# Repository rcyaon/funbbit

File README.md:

# Funbbit

A modern recreation of the Sony PET-F7 "Funbbit" (1998): a virtual-pet
accessory for a Walkman (or any 3.5 mm player). It sits inline between the
player and the headphones, taps the audio without disturbing it, and animates
a pet on a 1.28" Sharp monochrome memory LCD. The pet dances while music plays
("dancing pet", "weight battle") and gets fat when it does not. An STM32U083
runs everything from a single **CR2032** coin cell.

## Renders

| Top | Bottom |
| --- | --- |
|  |  |

44 x 72 mm, 2 layers, black mask, white silkscreen. The Sharp LCD (fitted by
hand into J4) and the CR2032 cell are not shown. 

## Pixel art

Pet sprites are drawn in [Aseprite](https://www.aseprite.org/).

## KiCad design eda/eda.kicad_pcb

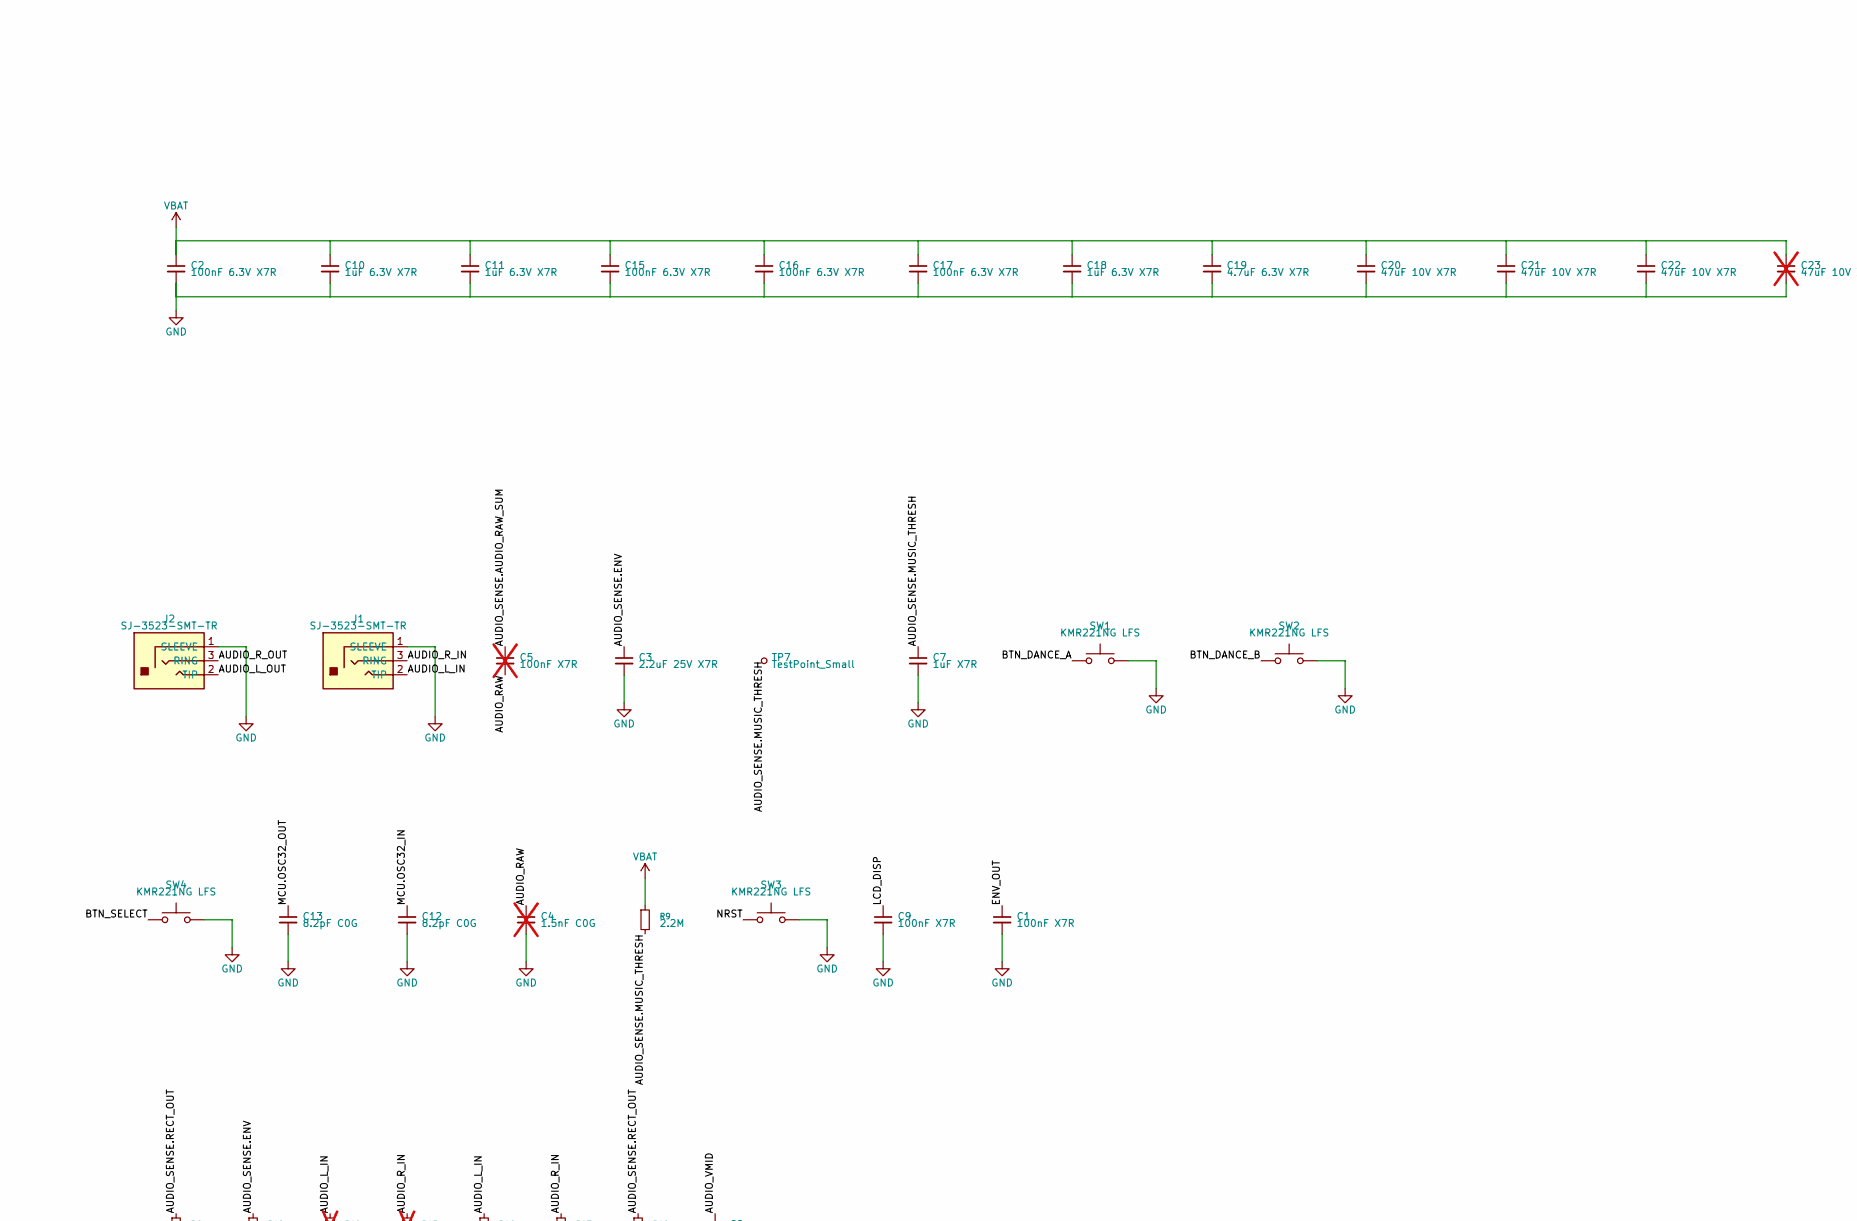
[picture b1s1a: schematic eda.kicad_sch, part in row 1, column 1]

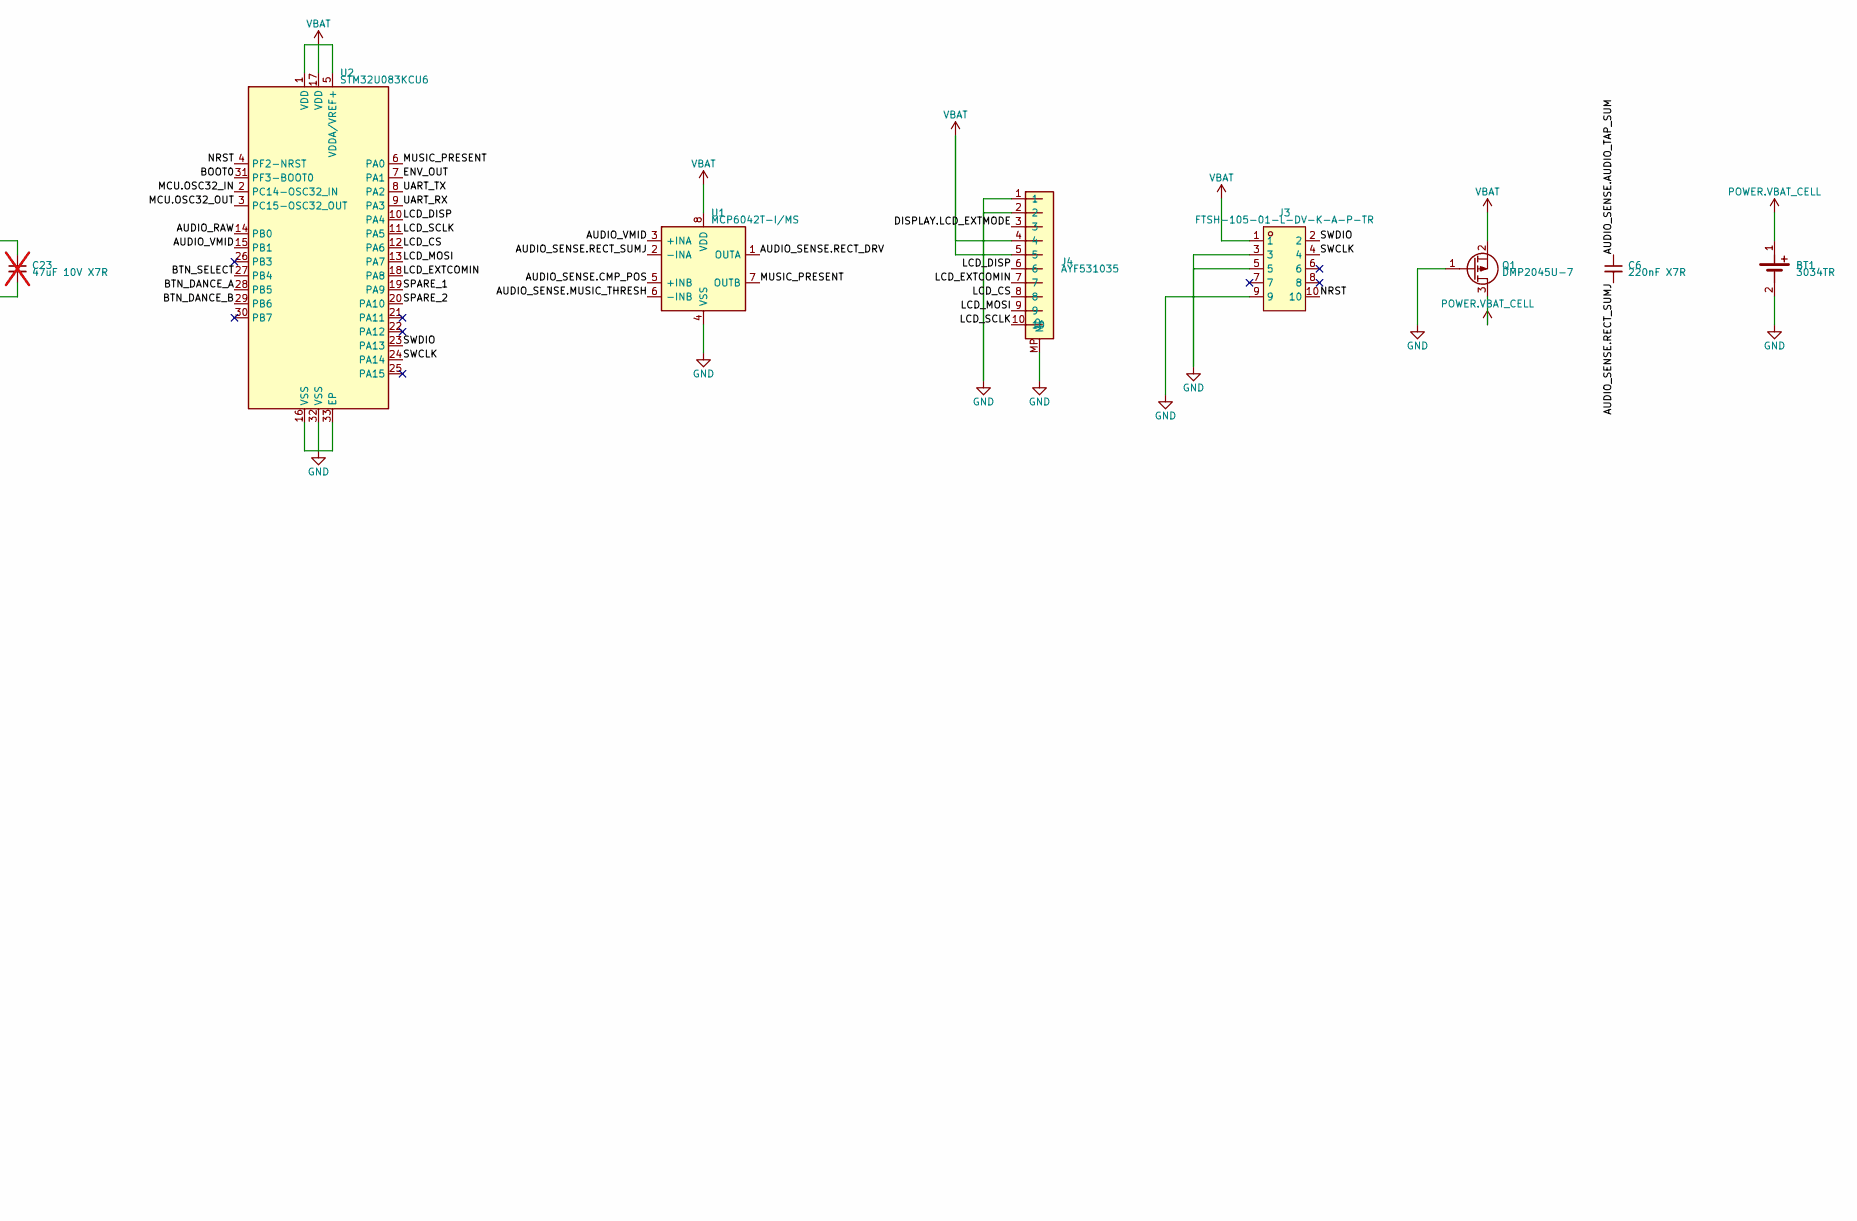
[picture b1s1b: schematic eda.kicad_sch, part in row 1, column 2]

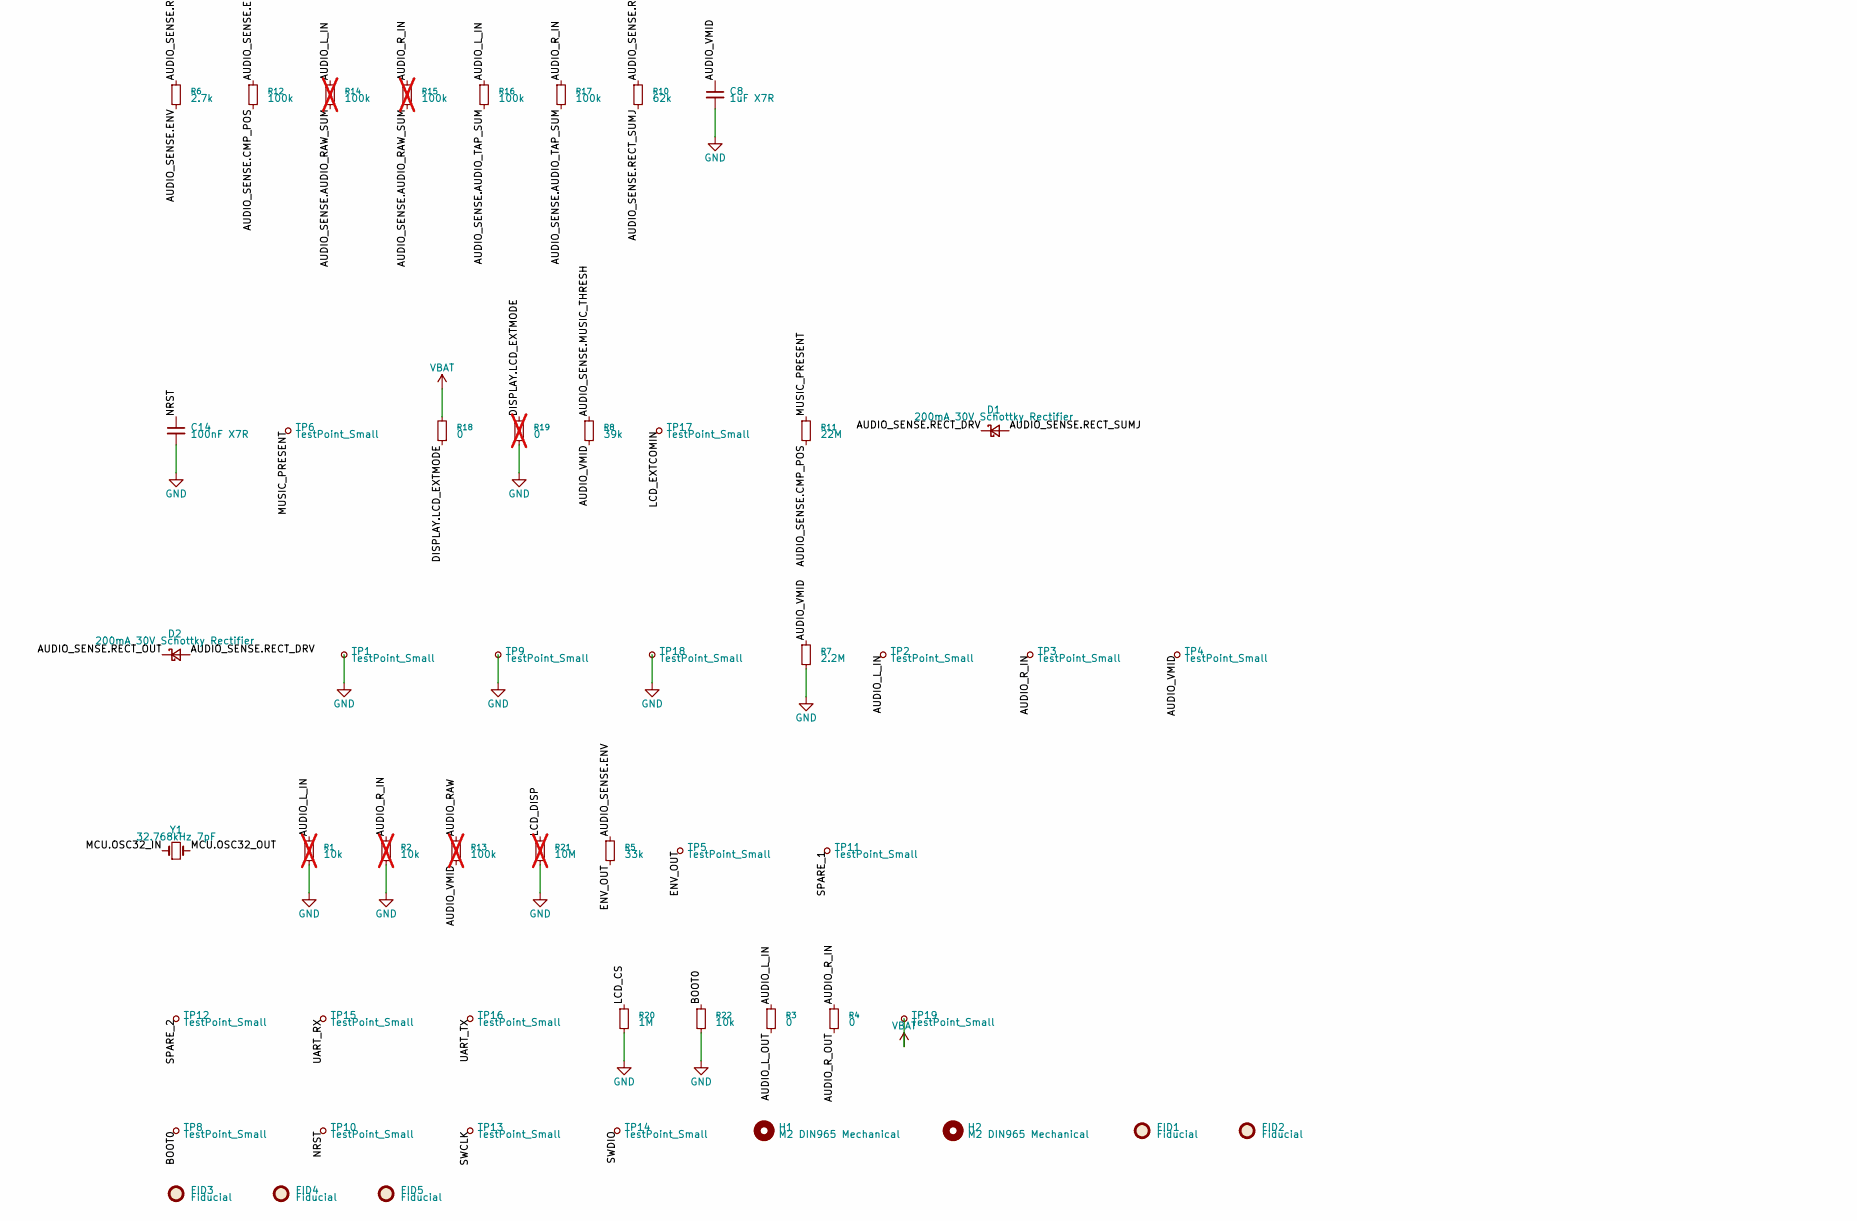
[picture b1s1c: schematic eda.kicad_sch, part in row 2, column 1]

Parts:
BT1: 3034TR; Keystone_3034
C1, C9, C14: 100nF X7R; C_0603_1608Metric
C2, C15, C16, C17: 100nF 6.3V X7R; C_0603_1608Metric
C3: 2.2uF 25V X7R; C_0603_1608Metric
C4: 1.5nF C0G; C_0603_1608Metric; not fitted
C5: 100nF X7R; C_0603_1608Metric; not fitted
C6: 220nF X7R; C_0603_1608Metric
C7, C8: 1uF X7R; C_0603_1608Metric
C10, C11, C18: 1uF 6.3V X7R; C_0603_1608Metric
C12, C13: 8.2pF C0G; C_0603_1608Metric
C19: 4.7uF 6.3V X7R; C_0603_1608Metric
C20, C21, C22: 47uF 10V X7R; C_1210_3225Metric
C23: 47uF 10V X7R; C_1210_3225Metric; not fitted
D1, D2: 200mA 30V Schottky Rectifier; D_SOD-323
FID1, FID2, FID3, FID4, FID5: Fiducial; Fiducial_1mm_Mask2mm
H1, H2: M2 DIN965 Mechanical; MountingHole_2.2mm_M2_DIN965
J1, J2: SJ-3523-SMT-TR; SJ-3523-SMT
J3: FTSH-105-01-L-DV-K-A-P-TR
J4: AYF531035
Q1: DMP2045U-7; SOT-23_Diodes_Standard
R1, R2: 10k; R_0603_1608Metric; not fitted
R3, R4, R18: 0; R_0603_1608Metric
R5: 33k; R_0603_1608Metric
R6: 2.7k; R_0603_1608Metric
R7, R9: 2.2M; R_0603_1608Metric
R8: 39k; R_0603_1608Metric
R10: 62k; R_0603_1608Metric
R11: 22M; R_0603_1608Metric
R12, R16, R17: 100k; R_0603_1608Metric
R13, R14, R15: 100k; R_0603_1608Metric; not fitted
R19: 0; R_0603_1608Metric; not fitted
R20: 1M; R_0603_1608Metric
R21: 10M; R_0603_1608Metric; not fitted
R22: 10k; R_0603_1608Metric
SW1, SW2, SW3, SW4: KMR221NG LFS; KMR2x1NGLFS
TP1, TP2, TP3: TestPoint_Small; TestPoint_THTPad_2.0x2.0mm_Drill1.0mm
TP4, TP5, TP6, TP7, TP8, TP9, TP10, TP11, TP12, TP13, TP14, TP15, TP16, TP17, TP18, TP19: TestPoint_Small; TestPoint_Pad_D1.5mm
U1: MCP6042T-I/MS; MSOP-8_3x3mm_P0.65mm_Microchip_MS
U2: STM32U083KCU6; ST_UFQFPN-32-1EP_5x5mm_P0.5mm_EP3.6x3.6mm
Y1: 32.768kHz 7pF; Crystal_SMD_3215-2Pin_3.2x1.5mm

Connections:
AUDIO_L_IN: J1.2 (TIP), R1.1, R3.1, R14.1, R16.1, TP2.1
AUDIO_L_OUT: J2.2 (TIP), R3.2
AUDIO_RAW: C4.1, C5.2, R13.1, U2.14 (PB0)
AUDIO_R_IN: J1.3 (RING), R2.1, R4.1, R15.1, R17.1, TP3.1
AUDIO_R_OUT: J2.3 (RING), R4.2
AUDIO_SENSE.AUDIO_RAW_SUM: C5.1, R14.2, R15.2
AUDIO_SENSE.AUDIO_TAP_SUM: C6.1, R16.2, R17.2
AUDIO_SENSE.CMP_POS: R11.2, R12.2, U1.5 (+INB)
AUDIO_SENSE.ENV: C3.1, R5.1, R6.2, R12.1
AUDIO_SENSE.MUSIC_THRESH: C7.1, R8.1, R9.2, TP7.1, U1.6 (-INB)
AUDIO_SENSE.RECT_DRV: D1.1 (K), D2.2 (A), U1.1 (OUTA)
AUDIO_SENSE.RECT_OUT: D2.1 (K), R6.1, R10.1
AUDIO_SENSE.RECT_SUMJ: C6.2, D1.2 (A), R10.2, U1.2 (-INA)
AUDIO_VMID: C8.1, R7.1, R8.2, R13.2, TP4.1, U1.3 (+INA), U2.15 (PB1)
BOOT0: R22.1, TP8.1, U2.31 (PF3-BOOT0)
BTN_DANCE_A: SW1.1, SW1.4 (1), U2.28 (PB5)
BTN_DANCE_B: SW2.1, SW2.4 (1), U2.29 (PB6)
BTN_SELECT: SW4.1, SW4.4 (1), U2.27 (PB4)
DEBUG.J_SWD.NC_J_6: J3.6
DEBUG.J_SWD.NC_J_7: J3.7
DEBUG.J_SWD.NC_J_8: J3.8
DISPLAY.LCD_EXTMODE: J4.3, R18.1, R19.1
ENV_OUT: C1.1, R5.2, TP5.1, U2.7 (PA1)
GND: BT1.2 (NEG), C1.2, C2.2, C3.2, C4.2, C7.2, C8.2, C9.2, C10.2, C11.2, C12.2, C13.2, C14.2, C15.2, C16.2, C17.2, C18.2, C19.2, C20.2, C21.2, C22.2, C23.2, J1.1 (SLEEVE), J2.1 (SLEEVE), J3.3, J3.5, J3.9, J4.1, J4.2, J4.MP, Q1.1 (G), R1.2, R2.2, R7.2, R19.2, R20.2, R21.2, R22.2, SW1.2, SW1.3 (2), SW2.2, SW2.3 (2), SW3.2, SW3.3 (2), SW4.2, SW4.3 (2), TP1.1, TP9.1, TP18.1, U1.4 (VSS), U2.16 (VSS), U2.32 (VSS), U2.33 (EP)
LCD_CS: J4.8, R20.1, U2.12 (PA6)
LCD_DISP: C9.1, J4.6, R21.1, U2.10 (PA4)
LCD_EXTCOMIN: J4.7, TP17.1, U2.18 (PA8)
LCD_MOSI: J4.9, U2.13 (PA7)
LCD_SCLK: J4.10, U2.11 (PA5)
MCU.OSC32_IN: C12.1, U2.2 (PC14-OSC32_IN), Y1.1
MCU.OSC32_OUT: C13.1, U2.3 (PC15-OSC32_OUT), Y1.2
MCU.U_MCU.NC_STM32U083KCU6_PA11: U2.21 (PA11)
MCU.U_MCU.NC_STM32U083KCU6_PA12: U2.22 (PA12)
MCU.U_MCU.NC_STM32U083KCU6_PA15: U2.25 (PA15)
MCU.U_MCU.NC_STM32U083KCU6_PB3: U2.26 (PB3)
MCU.U_MCU.NC_STM32U083KCU6_PB7: U2.30 (PB7)
MUSIC_PRESENT: R11.1, TP6.1, U1.7 (OUTB), U2.6 (PA0)
NRST: C14.1, J3.10, SW3.1, SW3.4 (1), TP10.1, U2.4 (PF2-NRST)
POWER.VBAT_CELL: BT1.1 (POS), Q1.3 (D)
SPARE_1: TP11.1, U2.19 (PA9)
SPARE_2: TP12.1, U2.20 (PA10)
SWCLK: J3.4, TP13.1, U2.24 (PA14)
SWDIO: J3.2, TP14.1, U2.23 (PA13)
UART_RX: TP15.1, U2.9 (PA3)
UART_TX: TP16.1, U2.8 (PA2)
VBAT: C2.1, C10.1, C11.1, C15.1, C16.1, C17.1, C18.1, C19.1, C20.1, C21.1, C22.1, C23.1, J3.1, J4.4, J4.5, Q1.2 (S), R9.1, R18.2, TP19.1, U1.8 (VDD), U2.1 (VDD), U2.5 (VDDA/VREF+), U2.17 (VDD)

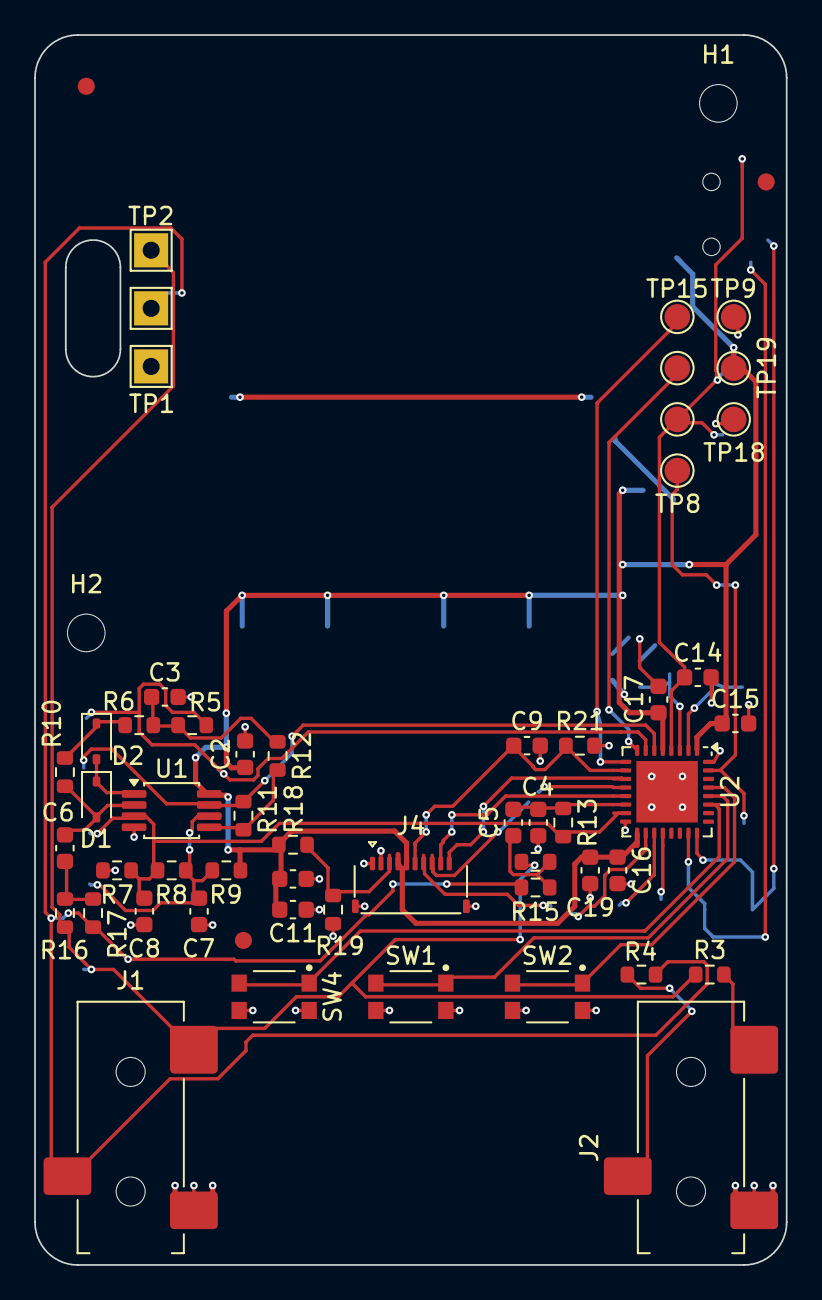
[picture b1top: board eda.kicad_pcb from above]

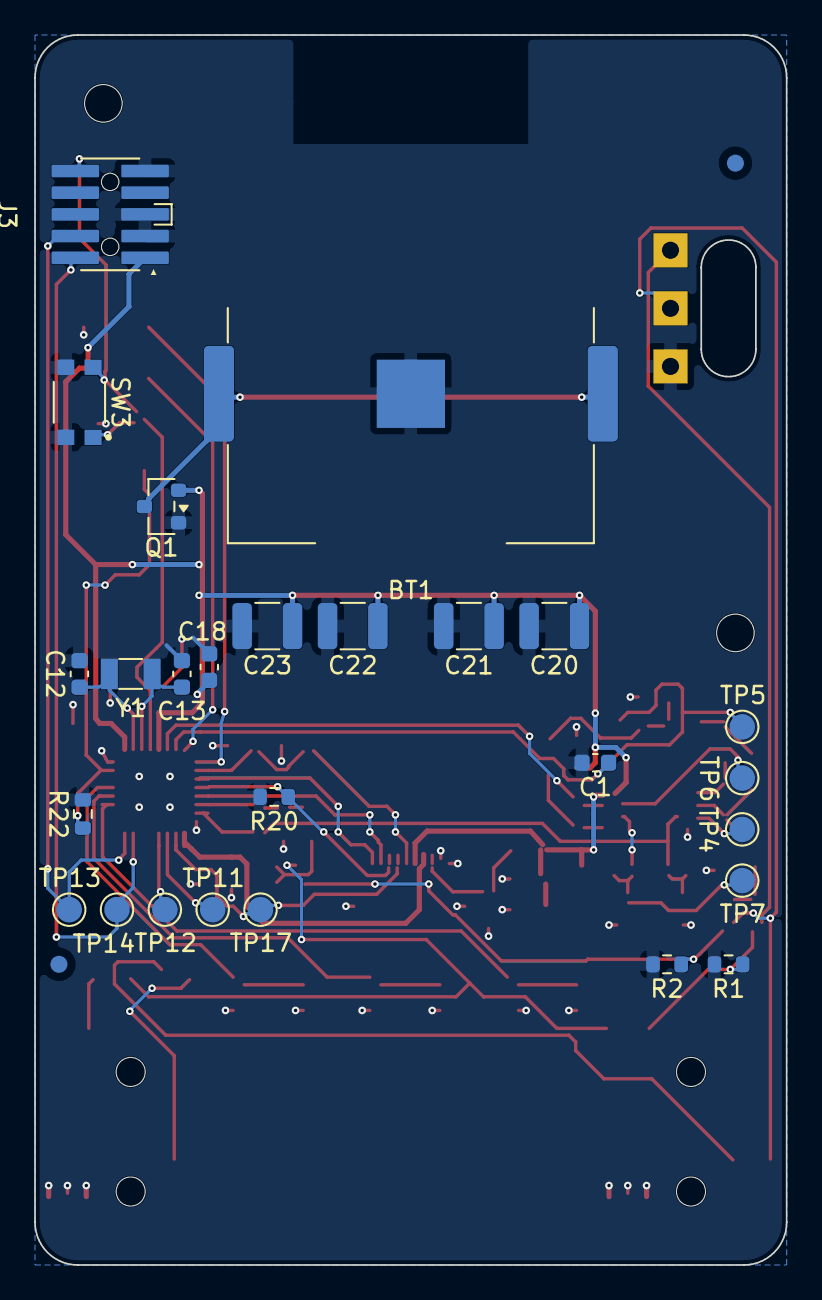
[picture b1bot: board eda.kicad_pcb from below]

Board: 2 copper layers, 44.0 x 72.0 mm, 86 parts (28 on the bottom side), 38 nets.

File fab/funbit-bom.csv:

Designators,Qty,DNP,Manufacturer,MPN,Value/Description,Package,DigiKey PN,Mouser PN,LCSC PN,US unit price (USD),US stock,Global stock,Match,Side,Instances,Notes
BT1,1,,Keystone Electronics,3034TR,"SMT retainer for one 20 mm coin cell (CR2032/CR2025/BR2016...), PCB pad is the negative contact",,36-3034TR-ND,534-3034TR,C5199422,0.29584,86600,97,MATCH_EXACT,bottom,POWER.BT_CELL,
C1 C2 C9 C14 C15 C16 C17,7,,Murata Electronics,GRM188R72A104KA35D,100nF X7R,0603,490-3285-1-ND,81-GRM188R72A104KA35,C77058,0.16,301134,89348,MATCH_COMPATIBLE,bottom/top,"AUDIO_SENSE.C_AA, AUDIO_SENSE.C_AFE_VDD, DISPLAY.C_LCD_DISP, MCU.C_NRST, MCU.C_VDD1, MCU.C_VDD17, MCU.C_VDDA",
C12 C13,2,,YAGEO,CC0603DRNPO9BN8R2,8.2pF C0G,0603,311-1742-1-ND,603-CC603DRNPO9BN8R2,C3847265,0.1,40638,326,MATCH_COMPATIBLE,bottom,"MCU.C_LSE_IN, MCU.C_LSE_OUT",
C19,1,,Murata Electronics,GRM188Z71C475KE21J,4.7uF 6.3V X7R,0603,490-GRM188Z71C475KE21JCT-ND,581-KAM15CR70J475MT,C389010,0.29,10000,58368,MATCH_COMPATIBLE,top,MCU.C_VDD_BULK,
C20 C21 C22,3,,Murata Electronics,GRM32ER71A476KE15L,47uF 10V X7R,1210,490-5312-1-ND,81-GRM32ER71A476KE5L,C84494,0.93,0,43824,MATCH_EXACT,bottom,"POWER.C_BULK1, POWER.C_BULK2, POWER.C_BULK3",No US distributor stock at last check; LCSC stocks it (Diode extended part). Any 47 uF 10 V X7R 1210 MLCC is an acceptable substitute.
C3,1,,Murata Electronics,GRM188Z71E225ME43D,2.2uF 25V X7R,0603,490-GRM188Z71E225ME43DCT-ND,81-GRM188Z71E225ME3D,C3856236,0.18,360903,4614,MATCH_COMPATIBLE,top,AUDIO_SENSE.C_ENV,
C6,1,,Murata Electronics,GCM188R71H224KA64D,220nF X7R,0603,490-5402-1-ND,81-GCM188R71H224K64D,C97857,0.17,502732,55430,MATCH_COMPATIBLE,top,AUDIO_SENSE.C_TAP_AC,
C7 C8 C10 C11 C18,5,,Murata Electronics,GCM188R71E105KA64D,1uF X7R,0603,490-10673-1-ND,81-GCM188R71E105KA4D,C85862,0.19,397758,111587,MATCH_COMPATIBLE,bottom/top,"AUDIO_SENSE.C_THRESH, AUDIO_SENSE.C_VMID, DISPLAY.C_LCD_VDD, DISPLAY.C_LCD_VDDA, MCU.C_VDDA_BULK",
D1 D2,2,,Vishay,BAT54WS-HE3_A-08,200mA 30V Schottky Rectifier,SOD-323,112-BAT54WS-HE3_A-08CT-ND,78-BAT54WS-HE3_A-08,C324473,0.49,13200,38837,MATCH_COMPATIBLE,top,"AUDIO_SENSE.D_CLAMP, AUDIO_SENSE.D_OUT",
J1 J2,2,,Same Sky,SJ-3523-SMT-TR,"3.5 mm stereo (TRS) audio jack, right angle, SMT, no switches",,CP-3523SJCT-ND,490-SJ-3523-SMT-TR,,0.88,80575,,MATCH_EXACT,top,"AUDIO_PASSTHROUGH.J_AUDIO_IN, AUDIO_PASSTHROUGH.J_AUDIO_OUT",
J3,1,,Samtec,FTSH-105-01-L-DV-K-A-P-TR,"Samtec FTSH series 2x5 1.27 mm (0.050"") pitch SMD pin header, 0.160"" mating height, with alignme ...",,SAM15419CT-ND,200-FTSH1051FDVKAPTR,C21318670,2.27,3715,30,MATCH_EXACT,bottom,DEBUG.J_SWD,Bottom side. Footprint v0.1.1: alignment holes 1.02 mm per Samtec layout Rev H.
J4,1,,Panasonic Industry,AYF531035,"10-position 0.5 mm pitch FPC/FFC connector, top and bottom contacts, back lock, SMT, 1.0 mm high",,255-AYF531035CT-ND,679-AYF531035A,C425133,0.88,9942,4886,MATCH_EXACT,top,DISPLAY.J_LCD,
Q1,1,,Diodes Incorporated,DMP2045U-7,"P-channel enhancement MOSFET, -20V, -4.3A, 45mOhm @ -4.5V, ESD-protected gate, SOT-23",,DMP2045U-7DICT-ND,621-DMP2045U-7,C459541,0.44,100676,14581,MATCH_EXACT,bottom,POWER.Q_REVERSE,
R10,1,,Panasonic Industry,ERJ-3EKF6202V,62k,0603,P62.0KHCT-ND,667-ERJ-3EKF6202V,C403306,0.1,51856,4871,MATCH_COMPATIBLE,top,AUDIO_SENSE.R_FB,
R11,1,,UNI-ROYAL(Uniroyal Elec),0603WAF2205T5E,22M,0603,,303-0603WAF2205T5E,C3000522,0.006999999999999999,5000,402046,MATCH_COMPATIBLE,top,AUDIO_SENSE.R_HYS_FB,
R12 R16 R17,3,,Panasonic Industry,ERJ-3EKF1003V,100k,0603,13-RT0603FRE13100KLCT-ND,667-ERJ-3EKF1003V,C189597,0.1,86198,747115,MATCH_COMPATIBLE,top,"AUDIO_SENSE.R_HYS_IN, AUDIO_SENSE.R_TAP_L, AUDIO_SENSE.R_TAP_R",
R20,1,,Panasonic Industry,ERJ-3EKF1004V,1M,0603,P1.00MHCT-ND,667-ERJ-3EKF1004V,C193390,0.1,1369353,816,MATCH_COMPATIBLE,bottom,DISPLAY.R_LCD_CS_PD,
R22,1,,Panasonic Industry,ERJ-3EKF1002V,10k,0603,P10.0KHCT-ND,667-ERJ-3EKF1002V,C191124,0.1,2132308,435486,MATCH_COMPATIBLE,bottom,MCU.R_BOOT0,
R3 R4 R18,3,,Panasonic Industry,ERJ-3GEY0R00V,0,0603,P0.0GCT-ND,667-ERJ-3GEY0R00V,C122704,0.1,4783703,262910,MATCH_COMPATIBLE,top,"AUDIO_PASSTHROUGH.R_LINK_L, AUDIO_PASSTHROUGH.R_LINK_R, DISPLAY.R_EXTMODE_HI",R18 (fitted) and R19 (DNP) are mutually exclusive LCD EXTMODE straps: never fit both (shorts VBAT to GND).
R5,1,,Panasonic Industry,ERJ-3EKF3302V,33k,0603,P33.0KHCT-ND,667-ERJ-3EKF3302V,C278619,0.1,145048,20009,MATCH_COMPATIBLE,top,AUDIO_SENSE.R_AA,
R6,1,,Panasonic Industry,ERJ-3EKF2701V,2.7k,0603,P2.70KHCT-ND,667-ERJ-3EKF2701V,C403121,0.11,92881,43480,MATCH_COMPATIBLE,top,AUDIO_SENSE.R_ATT,
R7 R9,2,,YAGEO,RC0603FR-132M2L,2.2M,0603,13-RC0603FR-132M2LCT-ND,603-RC0603FR-132M2L,C22938,0.1,30051,227380,MATCH_COMPATIBLE,top,"AUDIO_SENSE.R_BIAS_BOT, AUDIO_SENSE.R_BIAS_TOP",
R8,1,,Panasonic Industry,ERJ-3EKF3902V,39k,0603,P39.0KHCT-ND,667-ERJ-3EKF3902V,C278624,0.1,96376,19906,MATCH_COMPATIBLE,top,AUDIO_SENSE.R_BIAS_MID,
SW1 SW2 SW3 SW4,4,,C&K,KMR221NG LFS,"Tactile switch SPST-NO, 2N, 32V 50mA, silver contacts, IP40, 4.2x2.8mm SMD gullwing",,CKN10244CT-ND,611-KMR221NGLFS,C269272,0.67,80743,7233,MATCH_EXACT,bottom/top,"HMI.SW_DANCE_A, HMI.SW_DANCE_B, HMI.SW_RESET, HMI.SW_SELECT",
U1,1,,Microchip Technology,MCP6042T-I/MS,"Dual 600nA/ch, 14kHz, 1.4-6.0V rail-to-rail I/O CMOS op amp, MSOP-8",,MCP6042T-I/MSCT-ND,579-MCP6042T-I/MS,C627438,1.04,23176,461,MATCH_EXACT,top,AUDIO_SENSE.U_AFE,
U2,1,,STMicroelectronics,STM32U083KCU6,"STM32U083KC Arm Cortex-M0+ ultra-low-power MCU, 56 MHz, 256 KB flash, 40 KB SRAM, UFQFPN32 5x5 m ...",,497-STM32U083KCU6-ND,511-STM32U083KCU6,C22459164,3.8,13306,59,MATCH_EXACT,top,MCU.U_MCU,"DigiKey 497-STM32U083KCU6-ND currently 0 stock (364-day lead); buy from Mouser (13,306 in stock). STM32U073KCU6 is a pin-compatible no-AES alternate."
Y1,1,,Abracon LLC,ABS07-32.768KHZ-7-T,32.768kHz 7pF,3215_2Pin,535-9543-1-ND,815-ABS07-32.768K7T,C276424,0.86,401912,6373,MATCH_EXACT,bottom,MCU.Y_LSE,
C23,1,DNP,Murata Electronics,GRM32ER71A476KE15L,47uF 10V X7R,1210,490-5312-1-ND,81-GRM32ER71A476KE5L,C84494,0.93,0,43824,MATCH_EXACT,DNP,POWER.C_BULK4,No US distributor stock at last check; LCSC stocks it (Diode extended part). Any 47 uF 10 V X7R 1210 MLCC is an acceptable substitute.
C4,1,DNP,Murata Electronics,GRM1885C1H152JA01D,1.5nF C0G,0603,490-1455-1-ND,81-GRM1885C1H152JA01,C880279,0.1,871349,11758,MATCH_COMPATIBLE,DNP,AUDIO_SENSE.C_RAW_AA,
C5,1,DNP,Murata Electronics,GRM188R72A104KA35D,100nF X7R,0603,490-3285-1-ND,81-GRM188R72A104KA35,C77058,0.16,301134,89348,MATCH_COMPATIBLE,DNP,AUDIO_SENSE.C_RAW_AC,
R1 R2,2,DNP,Panasonic Industry,ERJ-3EKF1002V,10k,0603,P10.0KHCT-ND,667-ERJ-3EKF1002V,C191124,0.1,2132308,435486,MATCH_COMPATIBLE,DNP,"AUDIO_PASSTHROUGH.R_BLEED_L, AUDIO_PASSTHROUGH.R_BLEED_R",
R13 R14 R15,3,DNP,Panasonic Industry,ERJ-3EKF1003V,100k,0603,13-RT0603FRE13100KLCT-ND,667-ERJ-3EKF1003V,C189597,0.1,86198,747115,MATCH_COMPATIBLE,DNP,"AUDIO_SENSE.R_RAW_BIAS, AUDIO_SENSE.R_RAW_TAP_L, AUDIO_SENSE.R_RAW_TAP_R",
R19,1,DNP,Panasonic Industry,ERJ-3GEY0R00V,0,0603,P0.0GCT-ND,667-ERJ-3GEY0R00V,C122704,0.1,4783703,262910,MATCH_COMPATIBLE,DNP,DISPLAY.R_EXTMODE_LO,R18 (fitted) and R19 (DNP) are mutually exclusive LCD EXTMODE straps: never fit both (shorts VBAT to GND).
R21,1,DNP,YAGEO,RC0603FR-0710ML,10M,0603,311-10.0MHRCT-ND,603-RC0603FR-0710ML,C177620,0.1,47481,66968,MATCH_COMPATIBLE,DNP,DISPLAY.R_LCD_DISP_PD,
"(hand-fit, not SMT)",1,,Sharp,LS013B7DH03,"1.28in 128x128 reflective memory LCD, plugs into J4 (AYF531035)",FPC module,425-2903-ND,,,12.39,,,MATCH_EXACT,front (hand),DISPLAY (off-board),"Not soldered: insert FPC into J4 after assembly, then fix the glass with thin tape."

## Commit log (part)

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2026-04-30 Update project description for Sony CD Walkman
